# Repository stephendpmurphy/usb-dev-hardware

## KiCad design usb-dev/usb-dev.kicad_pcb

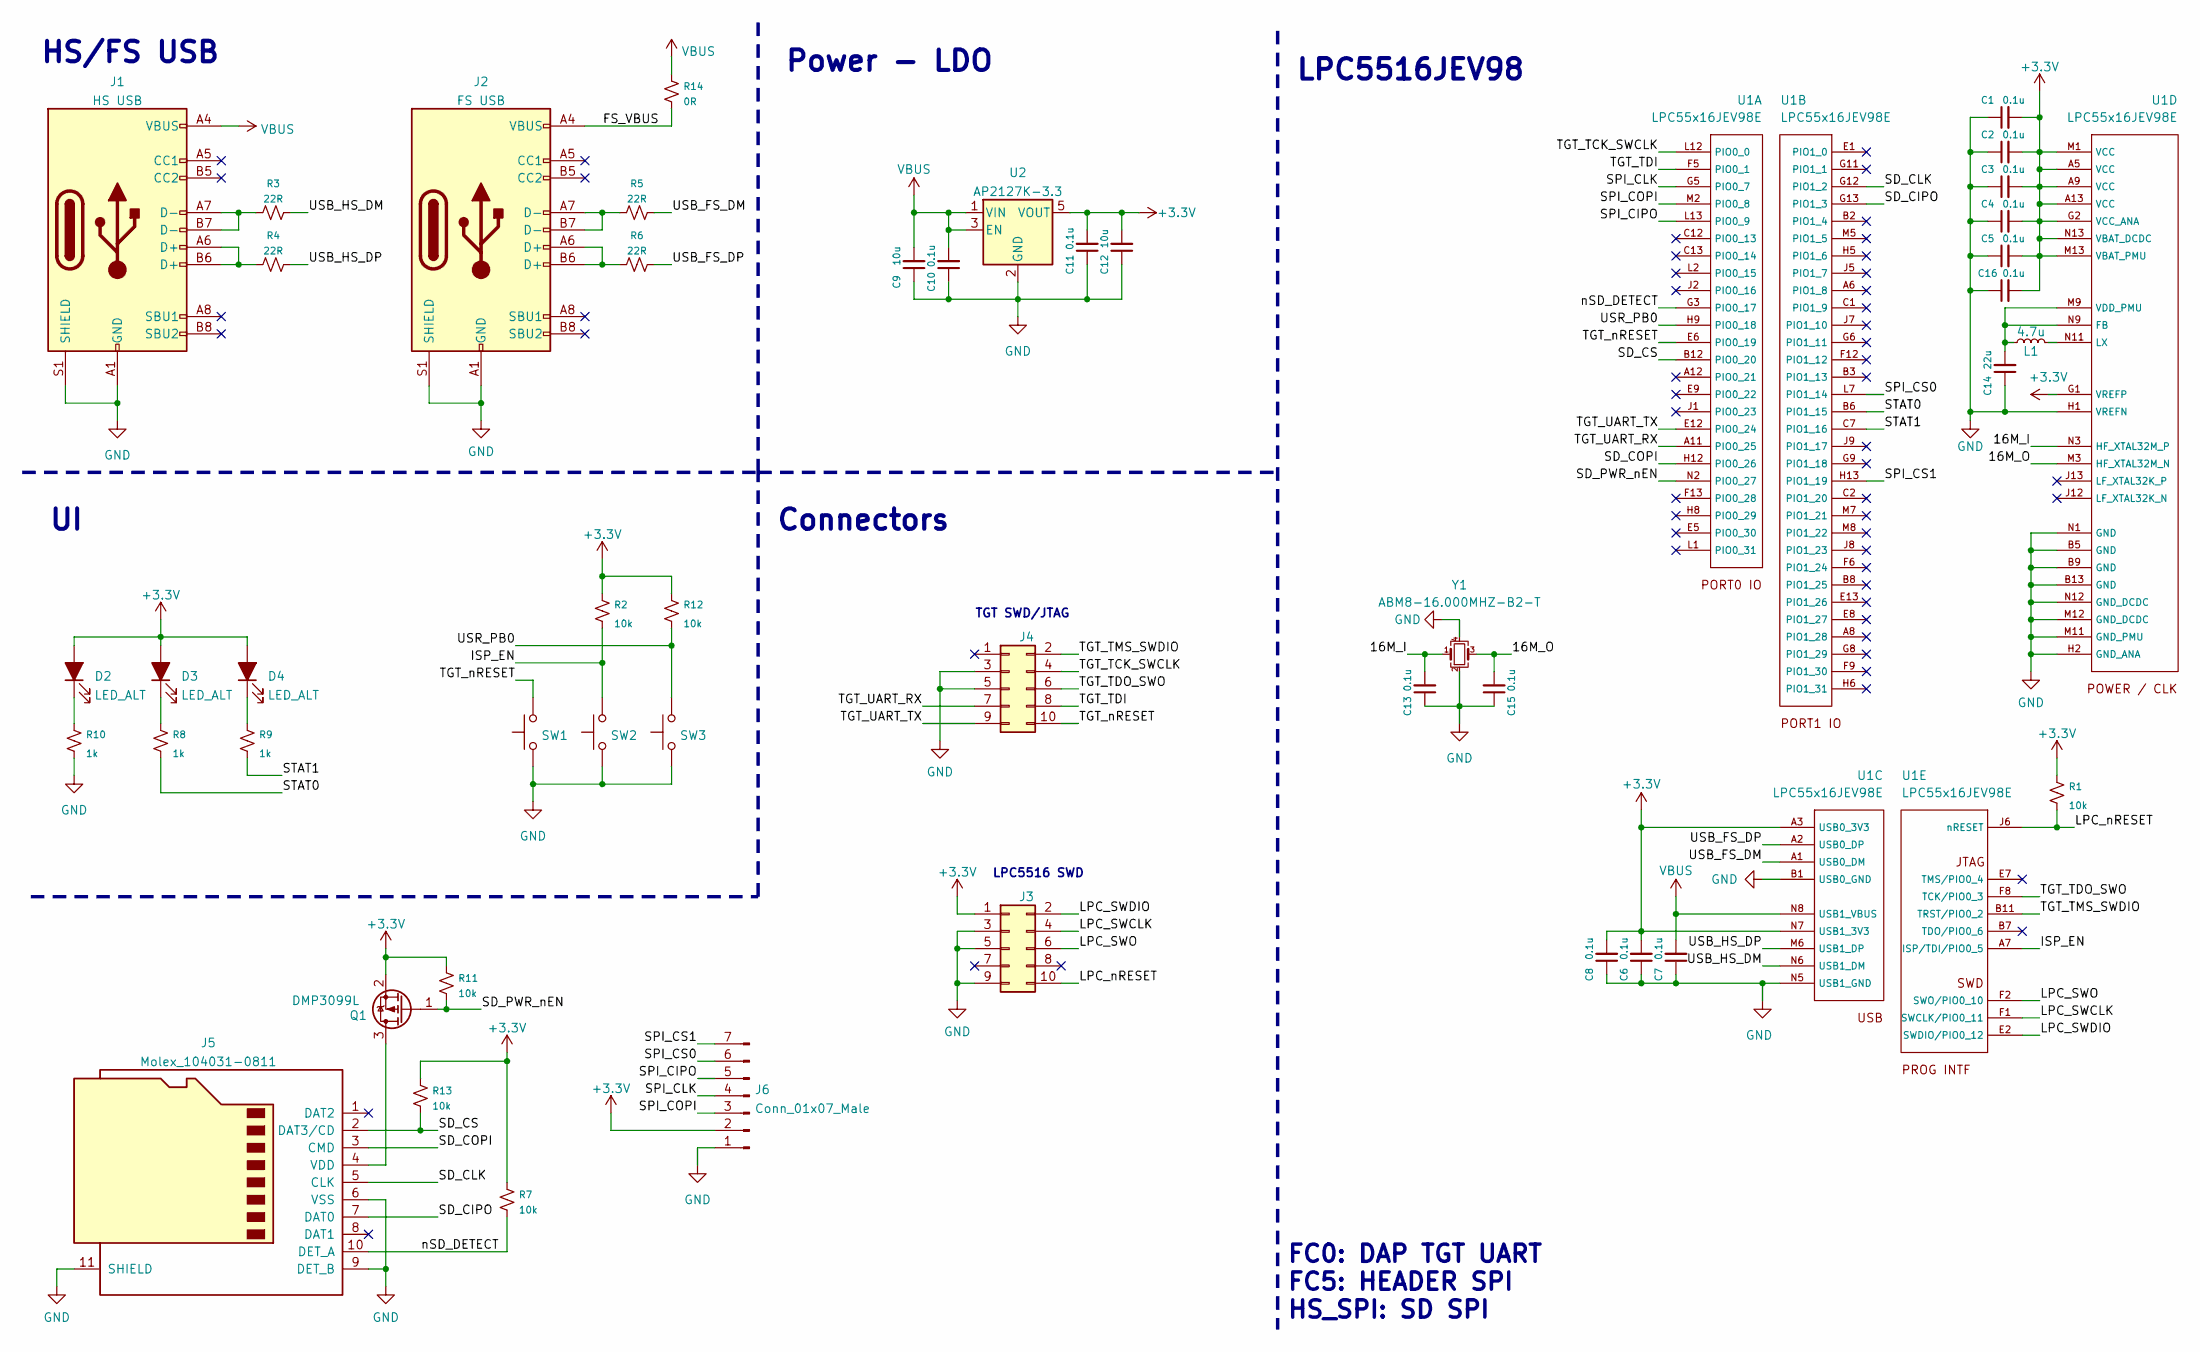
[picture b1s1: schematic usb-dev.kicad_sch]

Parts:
C1, C2, C3, C4, C5, C6, C7, C8, C10, C11, C13, C15, C16: 0.1u; C_0402_1005Metric
C9, C12: 10u; C_0402_1005Metric
C14: 22u; C_0402_1005Metric
D2, D3, D4: LED_ALT; LED_0402_1005Metric
J1: HS USB; USB_C_Receptacle_GCT_USB4085
J2: FS USB; USB_C_Receptacle_GCT_USB4085
J3, J4: Conn_02x05_Odd_Even; PinHeader_2x05_P1.27mm_Vertical_SMD
J5: Molex_104031-0811; microSD_HC_Molex_104031-0811
J6: Conn_01x07_Male; PinHeader_1x07_P2.54mm_Vertical
L1: 4.7u; L_0805_2012Metric
Q1: DMP3099L; SOT-23
R1, R2, R7, R11, R12, R13: 10k; R_0402_1005Metric
R3, R4, R5, R6: 22R; R_0402_1005Metric
R8, R9, R10: 1k; R_0402_1005Metric
R14: 0R; R_0402_1005Metric
SW1, SW2, SW3: SW_Push; Panasonic_EVQPUJ_EVQPUA
U1: LPC55x16JEV98E; BGA-98_13x13_7.0x7.0mm
U2: AP2127K-3.3; SOT-23-5
Y1: ABM8-16.000MHZ-B2-T; Crystal_SMD_3225-4Pin_3.2x2.5mm

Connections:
+3V3: C1.2, C2.2, C3.2, C4.2, C5.2, C6.2, C8.2, C11.2, C12.2, C16.2, D2.2 (A), D3.2 (A), D4.2 (A), J3.1, J6.2, Q1.2 (S), R1.1, R2.1, R7.2, R11.2, R12.1, R13.2, U1.A3 (USB0_3V3), U1.A5 (VCC), U1.A9 (VCC), U1.A13 (VCC), U1.G1 (VREFP), U1.G2 (VCC_ANA), U1.M1 (VCC), U1.M13 (VBAT_PMU), U1.N7 (USB1_3V3), U1.N13 (VBAT_DCDC), U2.5 (VOUT)
/16M_I: C13.2, U1.N3 (HF_XTAL32M_P), Y1.1
/16M_O: C15.2, U1.M3 (HF_XTAL32M_N), Y1.3
/FS_VBUS: J2.A4 (VBUS), J2.A9 (VBUS), J2.B4 (VBUS), J2.B9 (VBUS), R14.1
/ISP_EN: R2.2, SW2.2, U1.A7 (ISP/TDI/PIO0_5)
/LPC_SWCLK: J3.4, U1.F1 (SWCLK/PIO0_11)
/LPC_SWDIO: J3.2, U1.E2 (SWDIO/PIO0_12)
/LPC_SWO: J3.6, U1.F2 (SWO/PIO0_10)
/LPC_nRESET: J3.10, R1.2, U1.J6 (nRESET)
/SD_CIPO: J5.7 (DAT0), U1.G13 (PIO1_3)
/SD_CLK: J5.5 (CLK), U1.G12 (PIO1_2)
/SD_COPI: J5.3 (CMD), U1.H12 (PIO0_26)
/SD_CS: J5.2 (DAT3/CD), R13.1, U1.B12 (PIO0_20)
/SD_PWR_nEN: Q1.1 (G), R11.1, U1.N2 (PIO0_27)
/SPI_CIPO: J6.5, U1.L13 (PIO0_9)
/SPI_CLK: J6.4, U1.G5 (PIO0_7)
/SPI_COPI: J6.3, U1.M2 (PIO0_8)
/SPI_CS0: J6.6, U1.L7 (PIO1_14)
/SPI_CS1: J6.7, U1.H13 (PIO1_19)
/STAT0: R8.2, U1.B6 (PIO1_15)
/STAT1: R9.2, U1.C7 (PIO1_16)
/TGT_TCK_SWCLK: J4.4, U1.L12 (PIO0_0)
/TGT_TDI: J4.8, U1.F5 (PIO0_1)
/TGT_TDO_SWO: J4.6, U1.F8 (TCK/PIO0_3)
/TGT_TMS_SWDIO: J4.2, U1.B11 (TRST/PIO0_2)
/TGT_UART_RX: J4.7, U1.A11 (PIO0_25)
/TGT_UART_TX: J4.9, U1.E12 (PIO0_24)
/TGT_nRESET: J4.10, SW1.2, U1.E6 (PIO0_19)
/USB_FS_DM: R5.2, U1.A1 (USB0_DM)
/USB_FS_DP: R6.2, U1.A2 (USB0_DP)
/USB_HS_DM: R3.2, U1.N6 (USB1_DM)
/USB_HS_DP: R4.2, U1.M6 (USB1_DP)
/USR_PB0: R12.2, SW3.2, U1.H9 (PIO0_18)
/nSD_DETECT: J5.10 (DET_A), R7.1, U1.G3 (PIO0_17)
GND: C1.1, C2.1, C3.1, C4.1, C5.1, C6.1, C7.1, C8.1, C9.1, C10.1, C11.1, C12.1, C13.1, C14.1, C15.1, C16.1, J1.A1 (GND), J1.A12 (GND), J1.B1 (GND), J1.B12 (GND), J1.S1 (SHIELD), J2.A1 (GND), J2.A12 (GND), J2.B1 (GND), J2.B12 (GND), J2.S1 (SHIELD), J3.3, J3.5, J3.9, J4.3, J4.5, J5.6 (VSS), J5.9 (DET_B), J5.11 (SHIELD), J6.1, R10.2, SW1.1, SW2.1, SW3.1, U1.B1 (USB0_GND), U1.B5 (GND), U1.B9 (GND), U1.B13 (GND), U1.H1 (VREFN), U1.H2 (GND_ANA), U1.M11 (GND_PMU), U1.M12 (GND_DCDC), U1.N1 (GND), U1.N5 (USB1_GND), U1.N12 (GND_DCDC), U2.2 (GND), Y1.2, Y1.4
unnamed: C14.2, L1.1, U1.M9 (VDD_PMU), U1.N9 (FB)
unnamed: D2.1 (K), R10.1
unnamed: D3.1 (K), R8.1
unnamed: D4.1 (K), R9.1
unnamed: J1.A6 (D+), J1.B6 (D+), R4.1
unnamed: J1.A7 (D-), J1.B7 (D-), R3.1
unnamed: J2.A6 (D+), J2.B6 (D+), R6.1
unnamed: J2.A7 (D-), J2.B7 (D-), R5.1
unnamed: J5.4 (VDD), Q1.3 (D)
unnamed: L1.2, U1.N11 (LX)
VBUS: C7.2, C9.2, C10.2, J1.A4 (VBUS), J1.A9 (VBUS), J1.B4 (VBUS), J1.B9 (VBUS), R14.2, U1.N8 (USB1_VBUS), U2.1 (VIN), U2.3 (EN)

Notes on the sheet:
Connectors
HS/FS USB
FC0: DAP TGT UART FC5: HEADER SPI HS_SPI: SD SPI
Power - LDO
TGT SWD/JTAG
LPC5516 SWD
LPC5516JEV98

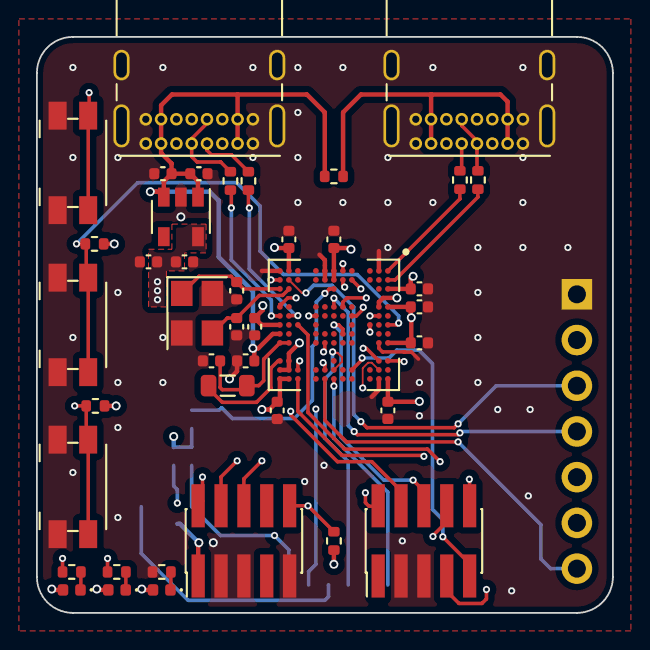
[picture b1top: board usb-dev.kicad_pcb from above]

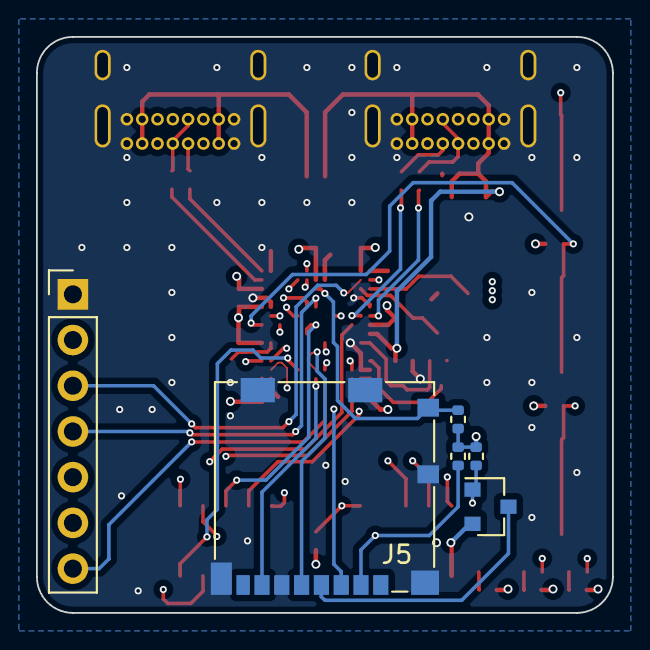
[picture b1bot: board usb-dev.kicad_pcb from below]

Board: 4 copper layers, 32.0 x 32.0 mm, 47 parts (6 on the bottom side), 46 nets.

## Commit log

2022-01-26 Initial commit - Clean ERC and DRC
2022-01-28 Clean ERC & DRC - Submitted to PCBWay
2022-02-06 Updating LPC BGA pad size to allow adequate space for soldermask in between pads
2022-02-21 Fixed VDD_PMU, added fet to SD power and added extra CS line to SPI header
2022-03-21 Fixed missing VDDCORE connections to internal switcher D:
